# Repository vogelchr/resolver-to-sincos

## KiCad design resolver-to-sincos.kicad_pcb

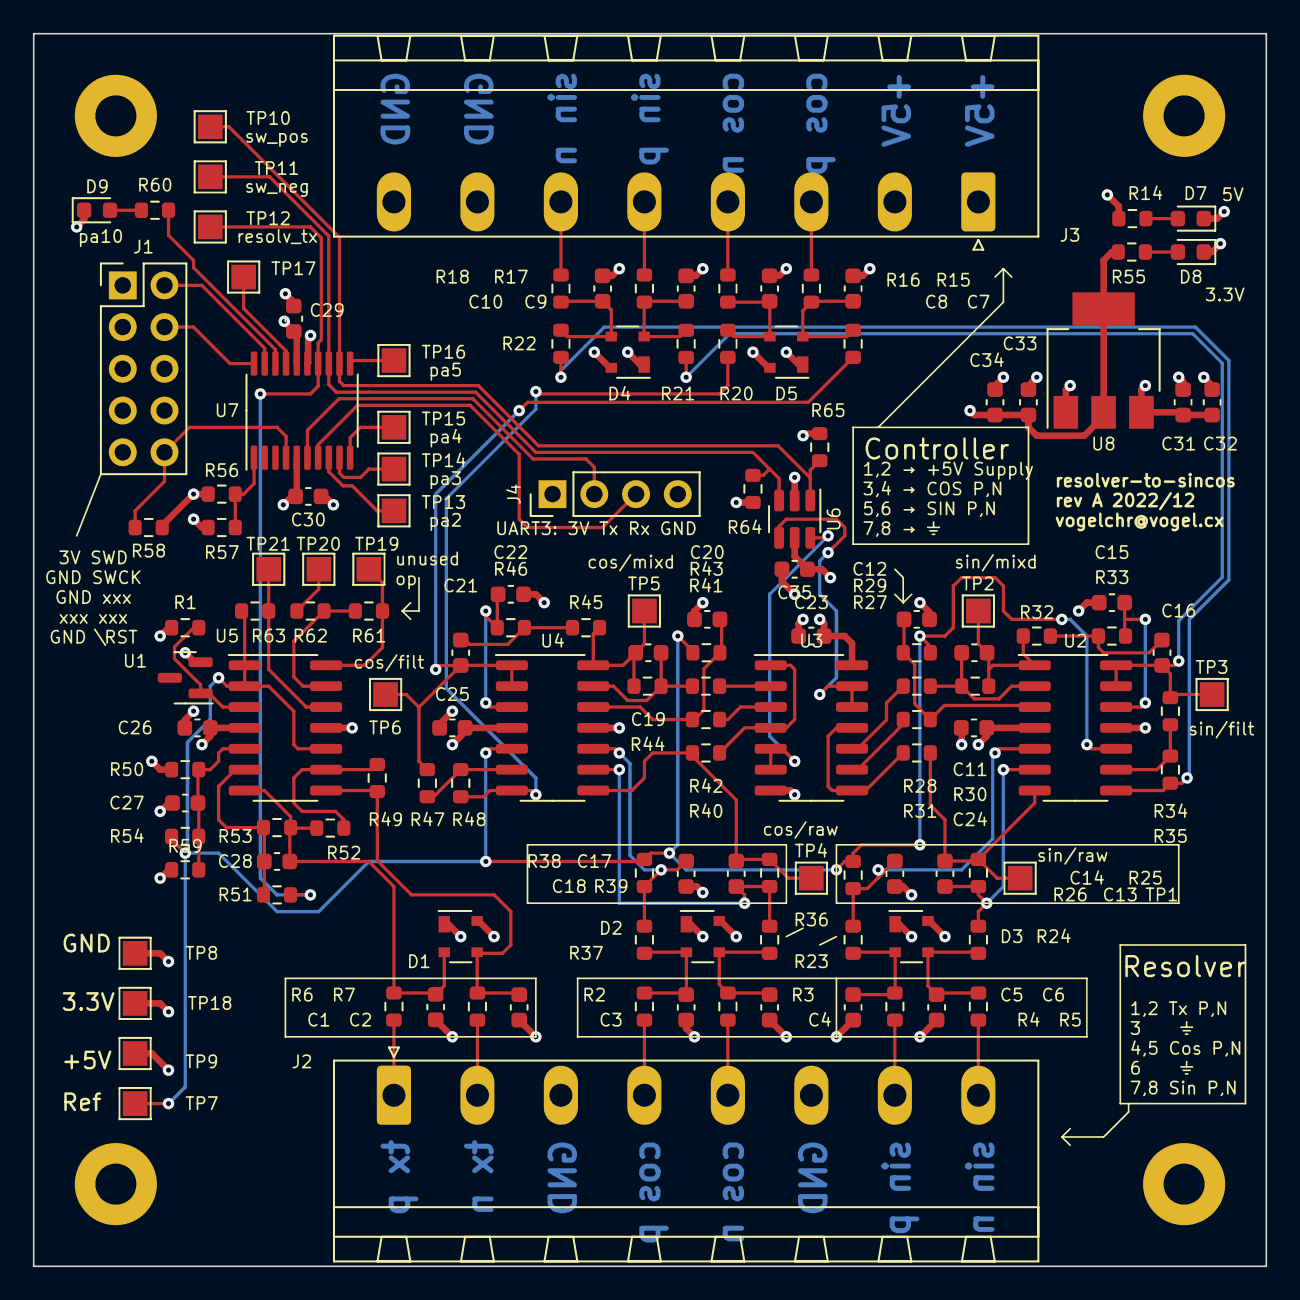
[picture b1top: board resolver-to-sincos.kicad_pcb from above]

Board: 4 copper layers, 75.0 x 75.0 mm, 139 parts (0 on the bottom side), 80 nets.

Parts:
C1, C2, C3, C4, C5, C6, C7, C8, C9, C10, C11, C12, C13, C17, C19, C20: 0.1n; C_0603_1608Metric
C14, C18, C27, C28: 1n0; C_0603_1608Metric
C15, C16, C21, C22: 10n; C_0603_1608Metric
C23, C24, C25, C26, C29, C30, C32, C33, C35: 100n; C_0603_1608Metric
C31, C34: 10u; C_0603_1608Metric
D1, D2, D3, D4, D5: PRTR5V0U2X; SOT-143
D7, D8, D9: LED_Small; LED_0603_1608Metric
H1, H2, H3, H4: MountingHole_Pad; MountingHole_2.5mm_Pad
J1: Conn_ARM_JTAG_SWD_10; PinHeader_2x05_P2.54mm_Vertical
J2, J3: Screw_Terminal_01x08; PhoenixContact_MSTBA_2,5_8-G-5,08_1x08_P5.08mm_Horizontal
J4: Conn_01x04; PinHeader_1x04_P2.54mm_Vertical
R1, R14, R55, R60: 1k; R_0603_1608Metric
R2, R3, R4, R5, R23, R24, R27, R28, R31, R36, R37, R40, R41, R42, R49, R51, R52, R53, R54, R61, R62, R63: 27k; R_0603_1608Metric
R6, R7, R15, R16, R17, R18, R19, R20, R21, R22: 68R; R_0603_1608Metric
R25, R26, R29, R30, R38, R39, R43, R44, R50, R56, R57, R58, R59, R64, R65: 51k; R_0603_1608Metric
R32, R33, R34, R35, R45, R46, R47, R48: 33k; R_0603_1608Metric
TP1, TP2, TP3, TP4, TP5, TP6, TP7, TP8, TP9, TP10, TP11, TP12, TP13, TP14, TP15, TP16, TP17, TP18, TP19, TP20, TP21: TestPoint; TestPoint_Pad_1.5x1.5mm
U1: LM4040DBZ-2.5; SOT-23
U2, U4, U5: MCP6484; SOIC-14_3.9x8.7mm_P1.27mm
U3: 4066; SOIC-14_3.9x8.7mm_P1.27mm
U6: 74LVC2G14; SOT-23-6
U7: STM32F030F4Px; TSSOP-20_4.4x6.5mm_P0.65mm
U8: AP1117-33; SOT-223-3_TabPin2

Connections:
+3.3V: C29.1, C30.2, C33.1, C34.1, J1.1 (VTref), J4.1, R50.1, R55.1, R56.1, R58.1, R64.1, R65.1, TP18.1, U7.5 (VDDA), U7.16 (VDD), U8.2 (VO)
+5V: C23.1, C24.1, C25.1, C26.1, C31.1, C32.1, C35.1, D1.4 (VCC), D2.4 (VCC), D3.4 (VCC), D4.4 (VCC), D5.4 (VCC), J3.1, J3.2, R1.1, R14.1, TP9.1, U2.4 (V+), U3.14 (VDD), U4.4 (V+), U5.4 (V+), U6.5 (VCC), U8.3 (VI)
/ESD_COSN: C8.1, D5.3 (I/O2), R16.1, R20.2
/ESD_COSP: C7.1, D5.2 (I/O1), R15.1, R19.2
/ESD_RCN: C4.1, D2.3 (I/O2), R3.2, R36.1
/ESD_RCP: C3.1, D2.2 (I/O1), R2.2, R37.1
/ESD_RSN: C6.1, D3.3 (I/O2), R5.2, R24.1
/ESD_RSP: C5.1, D3.2 (I/O1), R4.2, R23.1
/ESD_SINN: C10.1, D4.3 (I/O2), R18.1, R22.2
/ESD_SINP: C9.1, D4.2 (I/O1), R17.1, R21.2
/ESD_TXN: C2.1, D1.3 (I/O2), R7.2, R49.2, U5.8
/ESD_TXP: C1.1, C28.2, D1.2 (I/O1), R6.2, R52.1, R53.2, U5.7
/Microprocessor/SWCK: J1.4 (SWDCLK/TCK), U7.20 (PA14)
/Microprocessor/SWDIO: J1.2 (SWDIO/TMS), U7.19 (PA13)
/Microprocessor/SW_NEG_3v3: R64.2, TP11.1, U6.3, U7.13 (PA7)
/Microprocessor/SW_POS_3v3: R65.2, TP10.1, U6.1, U7.12 (PA6)
/Microprocessor/USART4_RX: J4.3, U7.7 (PA1)
/Microprocessor/USART4_TX: J4.2, U7.6 (PA0)
/Microprocessor/~RESET: J1.10 (~RESET), R58.2, U7.4 (NRST)
/OUT_COS_N: R20.1, R48.2, U4.7
/OUT_COS_P: C21.1, R19.1, R47.1, TP6.1, U4.1, U4.2 (-)
/OUT_SIN_N: R22.1, R35.2, U2.8
/OUT_SIN_P: C16.1, R21.1, R34.1, TP3.1, U2.13 (-), U2.14
/U_REF: R26.1, R29.1, R38.1, R43.1, R54.1, R63.1, TP7.1, U2.10 (+), U4.5 (+), U5.1, U5.2 (-), U5.10 (+)
GND: C1.2, C2.2, C3.2, C4.2, C5.2, C6.2, C7.2, C8.2, C9.2, C10.2, C12.1, C14.1, C15.1, C18.1, C20.1, C22.1, C23.2, C24.2, C25.2, C26.2, C27.1, C29.2, C30.1, C31.2, C32.2, C33.2, C34.2, C35.2, D1.1 (GND), D2.1 (GND), D3.1 (GND), D4.1 (GND), D5.1 (GND), D7.1 (K), D8.1 (K), D9.1 (K), H1.1, H2.1, H3.1, H4.1, J1.3 (GND), J1.5 (GND), J1.9 (GNDDetect), J2.3, J2.6, J3.7, J3.8, J4.4, R57.1, R59.1, TP8.1, U1.2 (A), U2.11 (V-), U3.7 (VSS), U4.11 (V-), U5.11 (V-), U6.2 (GND), U7.15 (VSS), U8.1 (GND)
unnamed: C11.2, R30.2, R32.1, TP2.1, U2.1
unnamed: C13.2, R25.2, R31.1, TP1.1, U2.7
unnamed: C16.2, R32.2, R33.1
unnamed: C17.2, R39.2, R40.1, TP4.1, U4.8
unnamed: C19.2, R44.2, R45.1, TP5.1, U4.14
unnamed: C21.2, R45.2, R46.1
unnamed: D7.2 (A), R14.2
unnamed: D8.2 (A), R55.2
unnamed: D9.2 (A), R60.2
unnamed: J2.1, R6.1
unnamed: J2.2, R7.1
unnamed: J2.4, R2.1
unnamed: J2.5, R3.1
unnamed: J2.7, R4.1
unnamed: J2.8, R5.1
unnamed: J3.3, R15.2
unnamed: J3.4, R16.2
unnamed: J3.5, R17.2
unnamed: J3.6, R18.2
unnamed: R27.1, U3.10
unnamed: R28.1, U3.9
unnamed: R31.2, U3.8, U3.11
unnamed: R40.2, U3.1, U3.4
unnamed: R41.1, U3.2
unnamed: R42.1, U3.3
unnamed: R61.2, TP19.1, U5.14
unnamed: R62.1, TP20.1
unnamed: R1.2, U1.1 (K), U5.3 (+)
unnamed: C12.2, R28.2, R29.2, U2.3 (+)
unnamed: C11.1, R27.2, R30.1, U2.2 (-)
unnamed: C14.2, R23.2, R26.2, U2.5 (+)
unnamed: C13.1, R24.2, R25.1, U2.6 (-)
unnamed: R34.2, R35.1, U2.9 (-)
unnamed: C15.2, R33.2, U2.12 (+)
unnamed: C22.2, R46.2, U4.3 (+)
unnamed: R47.2, R48.1, U4.6 (-)
unnamed: C18.2, R37.2, R38.2, U4.10 (+)
unnamed: C17.1, R36.2, R39.1, U4.9 (-)
unnamed: C20.2, R42.2, R43.2, U4.12 (+)
unnamed: C19.1, R41.2, R44.1, U4.13 (-)
unnamed: C27.2, R50.2, R54.2, R59.2, U5.5 (+)
unnamed: C28.1, R51.2, R53.1, U5.6 (-)
unnamed: R49.1, R52.2, U5.9 (-)
unnamed: R63.2, TP21.1, U5.12 (+)
unnamed: R61.1, R62.2, U5.13 (-)
unnamed: R56.2, R57.2, U7.1 (BOOT0)
unnamed: TP13.1, U7.8 (PA2)
unnamed: TP14.1, U7.9 (PA3)
unnamed: TP15.1, U7.10 (PA4)
unnamed: TP16.1, U7.11 (PA5)
unnamed: TP17.1, U7.17 (PA9)
unnamed: R60.1, U7.18 (PA10)
RESOLVER_TX: R51.1, TP12.1, U7.14 (PB1)
SW_NEG: U3.12, U3.13, U6.4
SW_POS: U3.5, U3.6, U6.6

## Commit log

2022-12-11 initially empty respository
2022-12-11 reva - draft
2022-12-11 cleanup rev-a
2022-12-11 gerbers, drills, schematic pdf for rev a
2022-12-11 reva - small tweaks
2022-12-24 Notes during bringup of rev. a.
2022-12-24 Start working on firmware for stm32f0
